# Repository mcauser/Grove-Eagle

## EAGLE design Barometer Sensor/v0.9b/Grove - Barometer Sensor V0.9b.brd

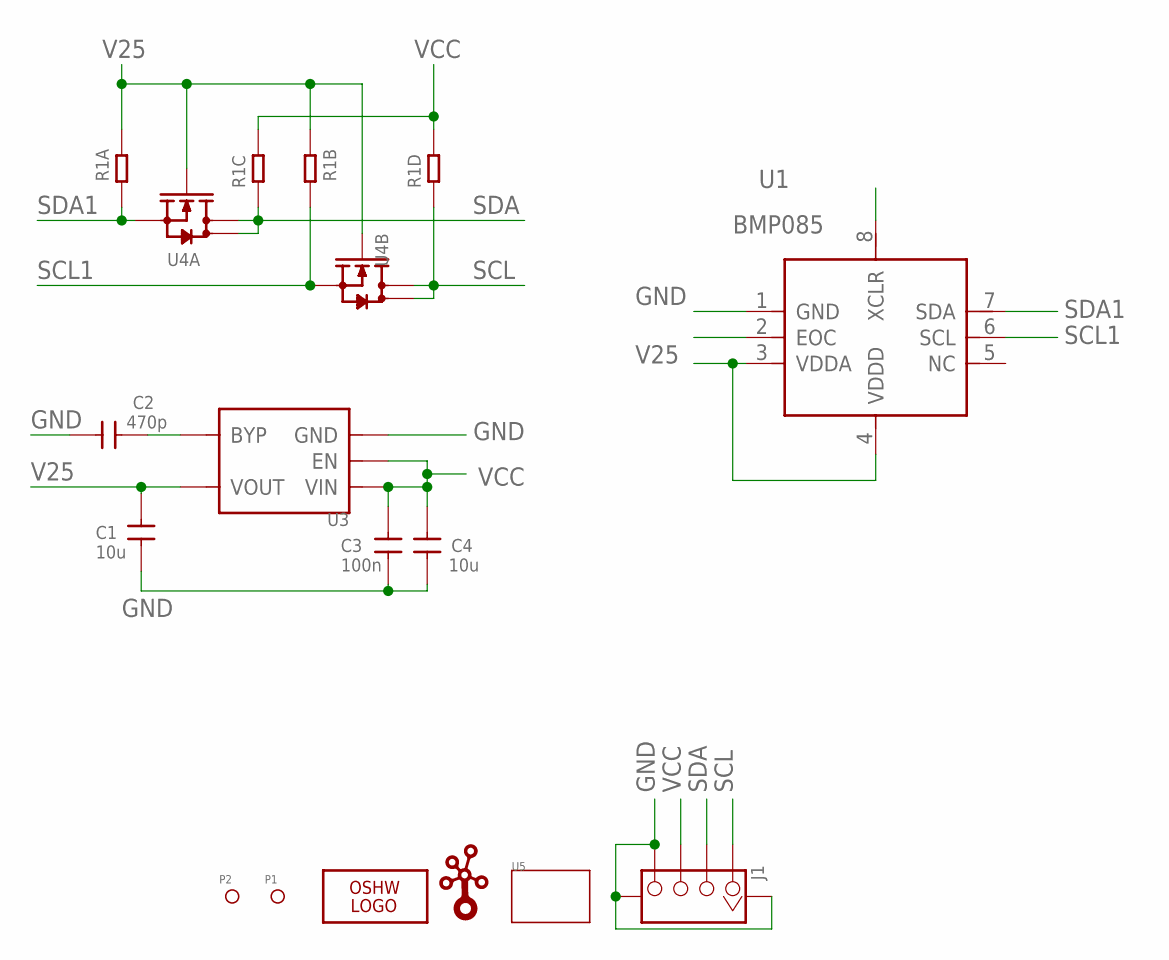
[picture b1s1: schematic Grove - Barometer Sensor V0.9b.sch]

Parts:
C1, C4: 10u; 0603
C2: 470p; 0603
C3: 100n; 0603
J1: TWIG-4P-2.0-SMD-FEMALE-REINFORCE'DD'; 4P-SMD-2.0
LOGO2: LOGO-OSHW-FILLX0200-NT; OSHW_FILLX200_NOTEXT
P1, P2: PAD-MARK; ROUND-MARK-0.635
R1: R-4R-1206; 1206-8-3.3X2.4
U1: BMP085; LCC8
U3: MIC5205; SOT23-5
U4: MOSFET-DUAL-N-1206-8; 1206-8
U5: TWIG-1U; 1U-DIM-W/-DRILL
U$1: LOGO-TWIGTWIGLOGO_SMALL; TWIGLOGO_SMALL

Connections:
GND: C1.2, C2.2, C3.1, C4.1, J1.4, J1.SS1, J1.SS2, U1.1 (GND), U3.2 (GND)
unnamed: C2.1, U3.4 (BYP)
SCL: J1.1, R1.4 (1), U4.5 (D), U4.6 (D)
SCL1: R1.7 (2), U1.6 (SCL), U4.3 (S)
SDA: J1.2, R1.3 (1), U4.7 (D), U4.8 (D)
SDA1: R1.1, U1.7 (SDA), U4.1 (S)
V25: C1.1, R1.2 (1), R1.8 (2), U1.3 (VDDA), U1.4 (VDDD), U3.5 (VOUT), U4.2 (G), U4.4 (G)
VCC: C3.2, C4.2, J1.3, R1.5 (2), R1.6 (2), U3.1 (VIN), U3.3 (EN)

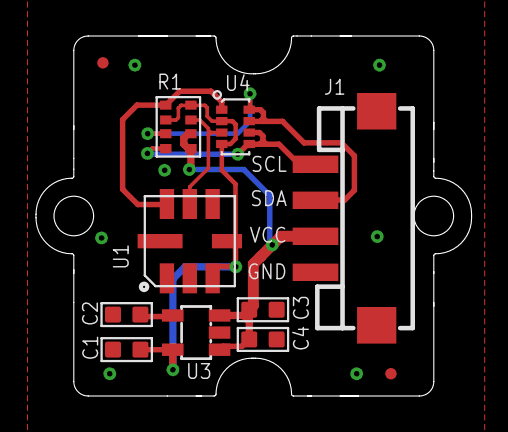
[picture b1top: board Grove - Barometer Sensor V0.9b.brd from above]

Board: 2 copper layers, 24.2 x 20.0 mm, 14 parts (2 on the bottom side), 8 nets.

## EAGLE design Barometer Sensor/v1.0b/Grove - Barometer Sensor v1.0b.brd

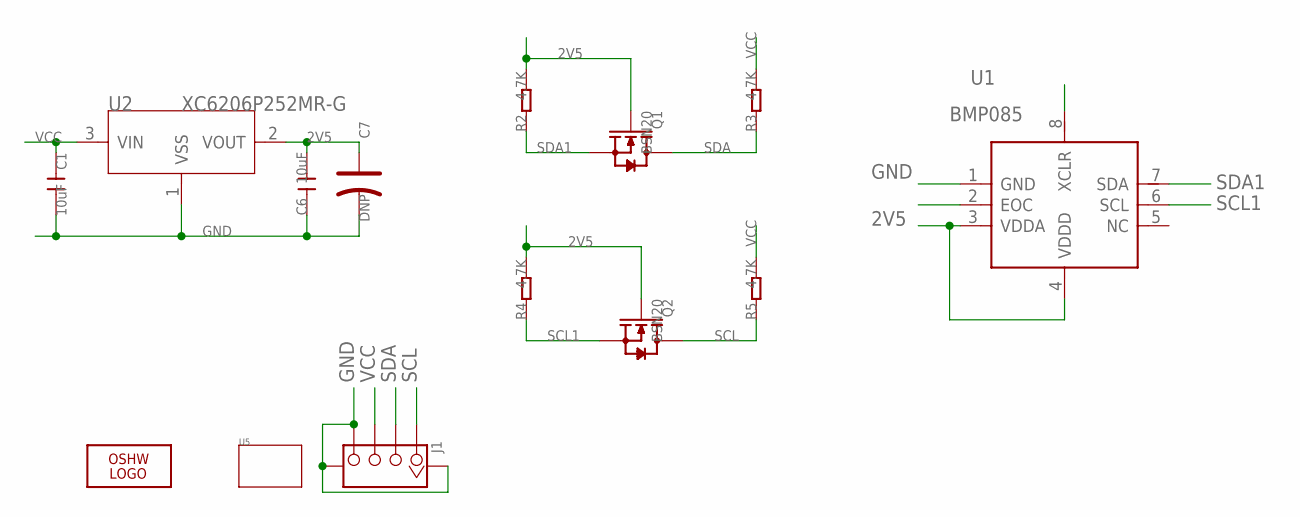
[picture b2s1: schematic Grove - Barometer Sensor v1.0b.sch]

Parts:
C1, C6: 10uF; C0805
C7: DNP; AVX-A
J1: TWIG-4P-2.0-SMD-FEMALE-REINFORCE'DD'; 4P-SMD-2.0
LOGO2: LOGO-OSHW-FILLX0200-NT; OSHW_FILLX200_NOTEXT
Q1, Q2: BSN20; SOT23
R2, R3, R4, R5: 4.7K; R0603
U1: BMP085; LCC8
U2: XC6206P252MR-G; SOT23
U5: TWIG-1U; 1U-DIM-W/-DRILL

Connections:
2V5: C6.2, C7.+, Q1.1 (G), Q2.1 (G), R2.2, R4.2, U1.3 (VDDA), U1.4 (VDDD), U2.2 (VOUT)
GND: C1.2, C6.1, C7.-, J1.4, J1.SS1, J1.SS2, U1.1 (GND), U2.1 (VSS)
SCL: J1.1, Q2.3 (D), R5.1
SCL1: Q2.2 (S), R4.1, U1.6 (SCL)
SDA: J1.2, Q1.3 (D), R3.1
SDA1: Q1.2 (S), R2.1, U1.7 (SDA)
VCC: C1.1, J1.3, R3.2, R5.2, U2.3 (VIN)

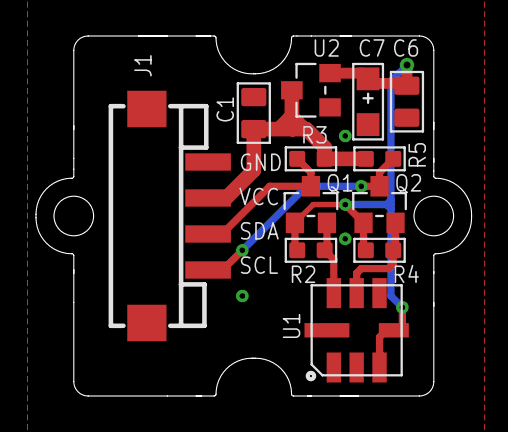
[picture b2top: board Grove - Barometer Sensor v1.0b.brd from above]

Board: 2 copper layers, 24.2 x 20.0 mm, 15 parts (2 on the bottom side), 7 nets.

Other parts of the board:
U$1: TWIGLOGO

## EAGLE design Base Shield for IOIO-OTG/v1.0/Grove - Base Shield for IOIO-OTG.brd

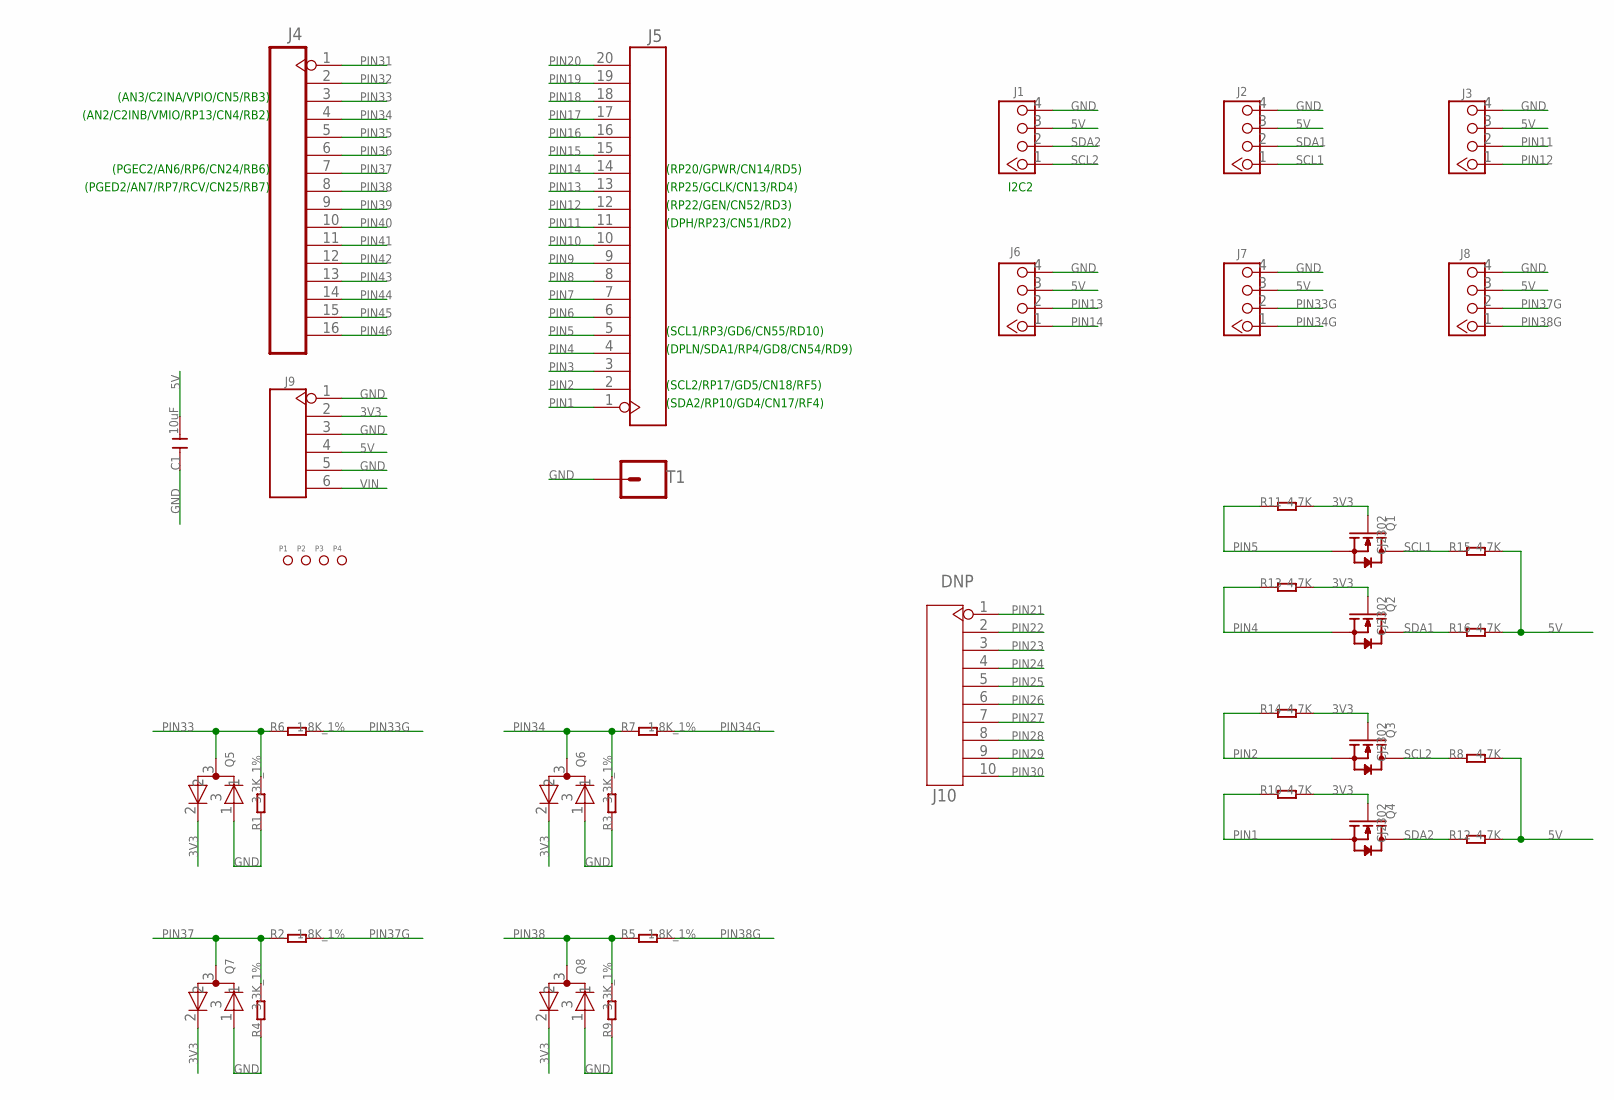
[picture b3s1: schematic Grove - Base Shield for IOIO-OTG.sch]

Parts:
C1: 10uF; C0805
J1, J2, J3, J6, J7, J8: TWIG-4P-2.0-2.0; 4P-2.0
J4: HEADER-16P-2.54; 16P-2.54
J5: HEADER-20P-2.54; 20P-2.54
J9: HEADER-6P-65/35MIL; 6P-2.54-65/35MIL
J10: DNP; 10P-2.54
P1, P2, P3, P4: PAD-MARK; ROUND-MARK-1.0
Q1, Q2, Q3, Q4: CJ2302; SOT23
Q5, Q6, Q7, Q8: BAV99; SOT23
R1, R3, R4, R9: 3.3K_1%; R0603
R2, R5, R6, R7: 1.8K_1%; R0603
R8, R10, R11, R12, R13, R14, R15, R16: 4.7K; R0603
T1: SPARKFUN_M01PTH; SPARKFUN_1X01

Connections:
3V3: J9.2, Q1.1 (G), Q2.1 (G), Q3.1 (G), Q4.1 (G), Q5.2, Q6.2, Q7.2, Q8.2, R10.2, R11.2, R13.2, R14.2
5V: C1.2, J1.3, J2.3, J3.3, J6.3, J7.3, J8.3, J9.4, R8.2, R12.2, R15.2, R16.2
GND: C1.1, J1.4, J2.4, J3.4, J6.4, J7.4, J8.4, J9.1, J9.3, J9.5, Q5.1, Q6.1, Q7.1, Q8.1, R1.1, R3.1, R4.1, R9.1, T1.1
PIN1: J5.1, Q4.2 (S), R10.1
PIN2: J5.2, Q3.2 (S), R14.1
PIN3: J5.3
PIN4: J5.4, Q2.2 (S), R13.1
PIN5: J5.5, Q1.2 (S), R11.1
PIN6: J5.6
PIN7: J5.7
PIN8: J5.8
PIN9: J5.9
PIN10: J5.10
PIN11: J3.2, J5.11
PIN12: J3.1, J5.12
PIN13: J5.13, J6.2
PIN14: J5.14, J6.1
PIN15: J5.15
PIN16: J5.16
PIN17: J5.17
PIN18: J5.18
PIN19: J5.19
PIN20: J5.20
PIN21: J10.1
PIN22: J10.2
PIN23: J10.3
PIN24: J10.4
PIN25: J10.5
PIN26: J10.6
PIN27: J10.7
PIN28: J10.8
PIN29: J10.9
PIN30: J10.10
PIN31: J4.1
PIN32: J4.2
PIN33: J4.3, Q5.3, R1.2, R6.1
PIN33G: J7.2, R6.2
PIN34: J4.4, Q6.3, R3.2, R7.1
PIN34G: J7.1, R7.2
PIN35: J4.5
PIN36: J4.6
PIN37: J4.7, Q7.3, R2.1, R4.2
PIN37G: J8.2, R2.2
PIN38: J4.8, Q8.3, R5.1, R9.2
PIN38G: J8.1, R5.2
PIN39: J4.9
PIN40: J4.10
PIN41: J4.11
PIN42: J4.12
PIN43: J4.13
PIN44: J4.14
PIN45: J4.15
PIN46: J4.16
SCL1: J2.1, Q1.3 (D), R15.1
SCL2: J1.1, Q3.3 (D), R8.1
SDA1: J2.2, Q2.3 (D), R16.1
SDA2: J1.2, Q4.3 (D), R12.1
VIN: J9.6

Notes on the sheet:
(SDA2/RP10/GD4/CN17/RF4)
(SCL2/RP17/GD5/CN18/RF5)
(SCL1/RP3/GD6/CN55/RD10)
(DPLN/SDA1/RP4/GD8/CN54/RD9)
(RP22/GEN/CN52/RD3)
(DPH/RP23/CN51/RD2)
(PGED2/AN7/RP7/RCV/CN25/RB7)
(PGEC2/AN6/RP6/CN24/RB6)
(RP20/GPWR/CN14/RD5)
(RP25/GCLK/CN13/RD4)
(AN2/C2INB/VMIO/RP13/CN4/RB2)
(AN3/C2INA/VPIO/CN5/RB3)
I2C2

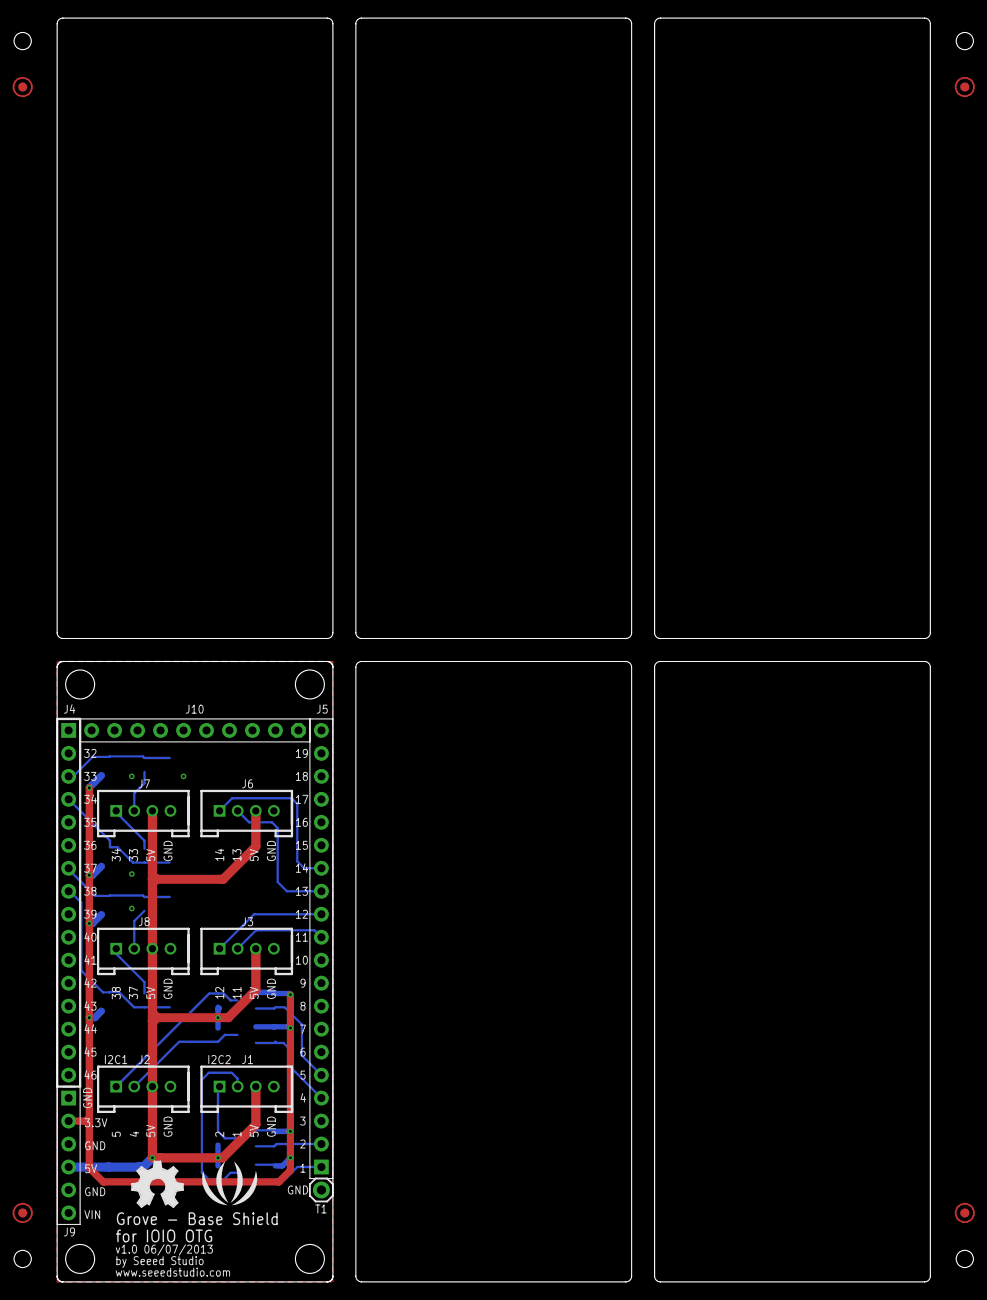
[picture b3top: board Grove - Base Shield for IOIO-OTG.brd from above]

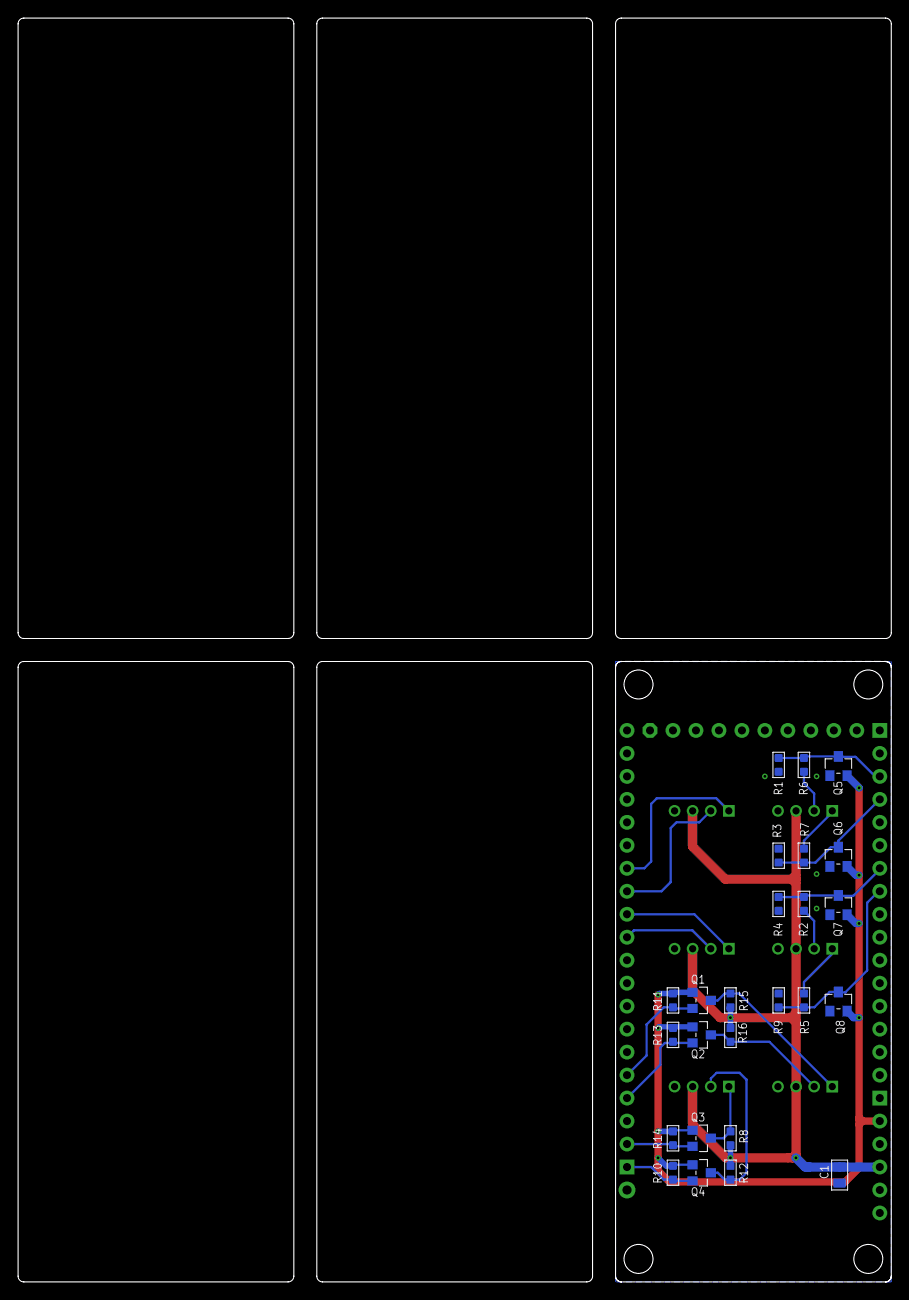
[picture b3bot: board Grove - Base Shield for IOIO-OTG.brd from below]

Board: 2 copper layers, 96.5 x 139.7 mm, 42 parts (25 on the bottom side), 23 nets.

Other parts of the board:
U$2: LOGO_SILK
U$3: OSHW_FILLX200_NOTEXT

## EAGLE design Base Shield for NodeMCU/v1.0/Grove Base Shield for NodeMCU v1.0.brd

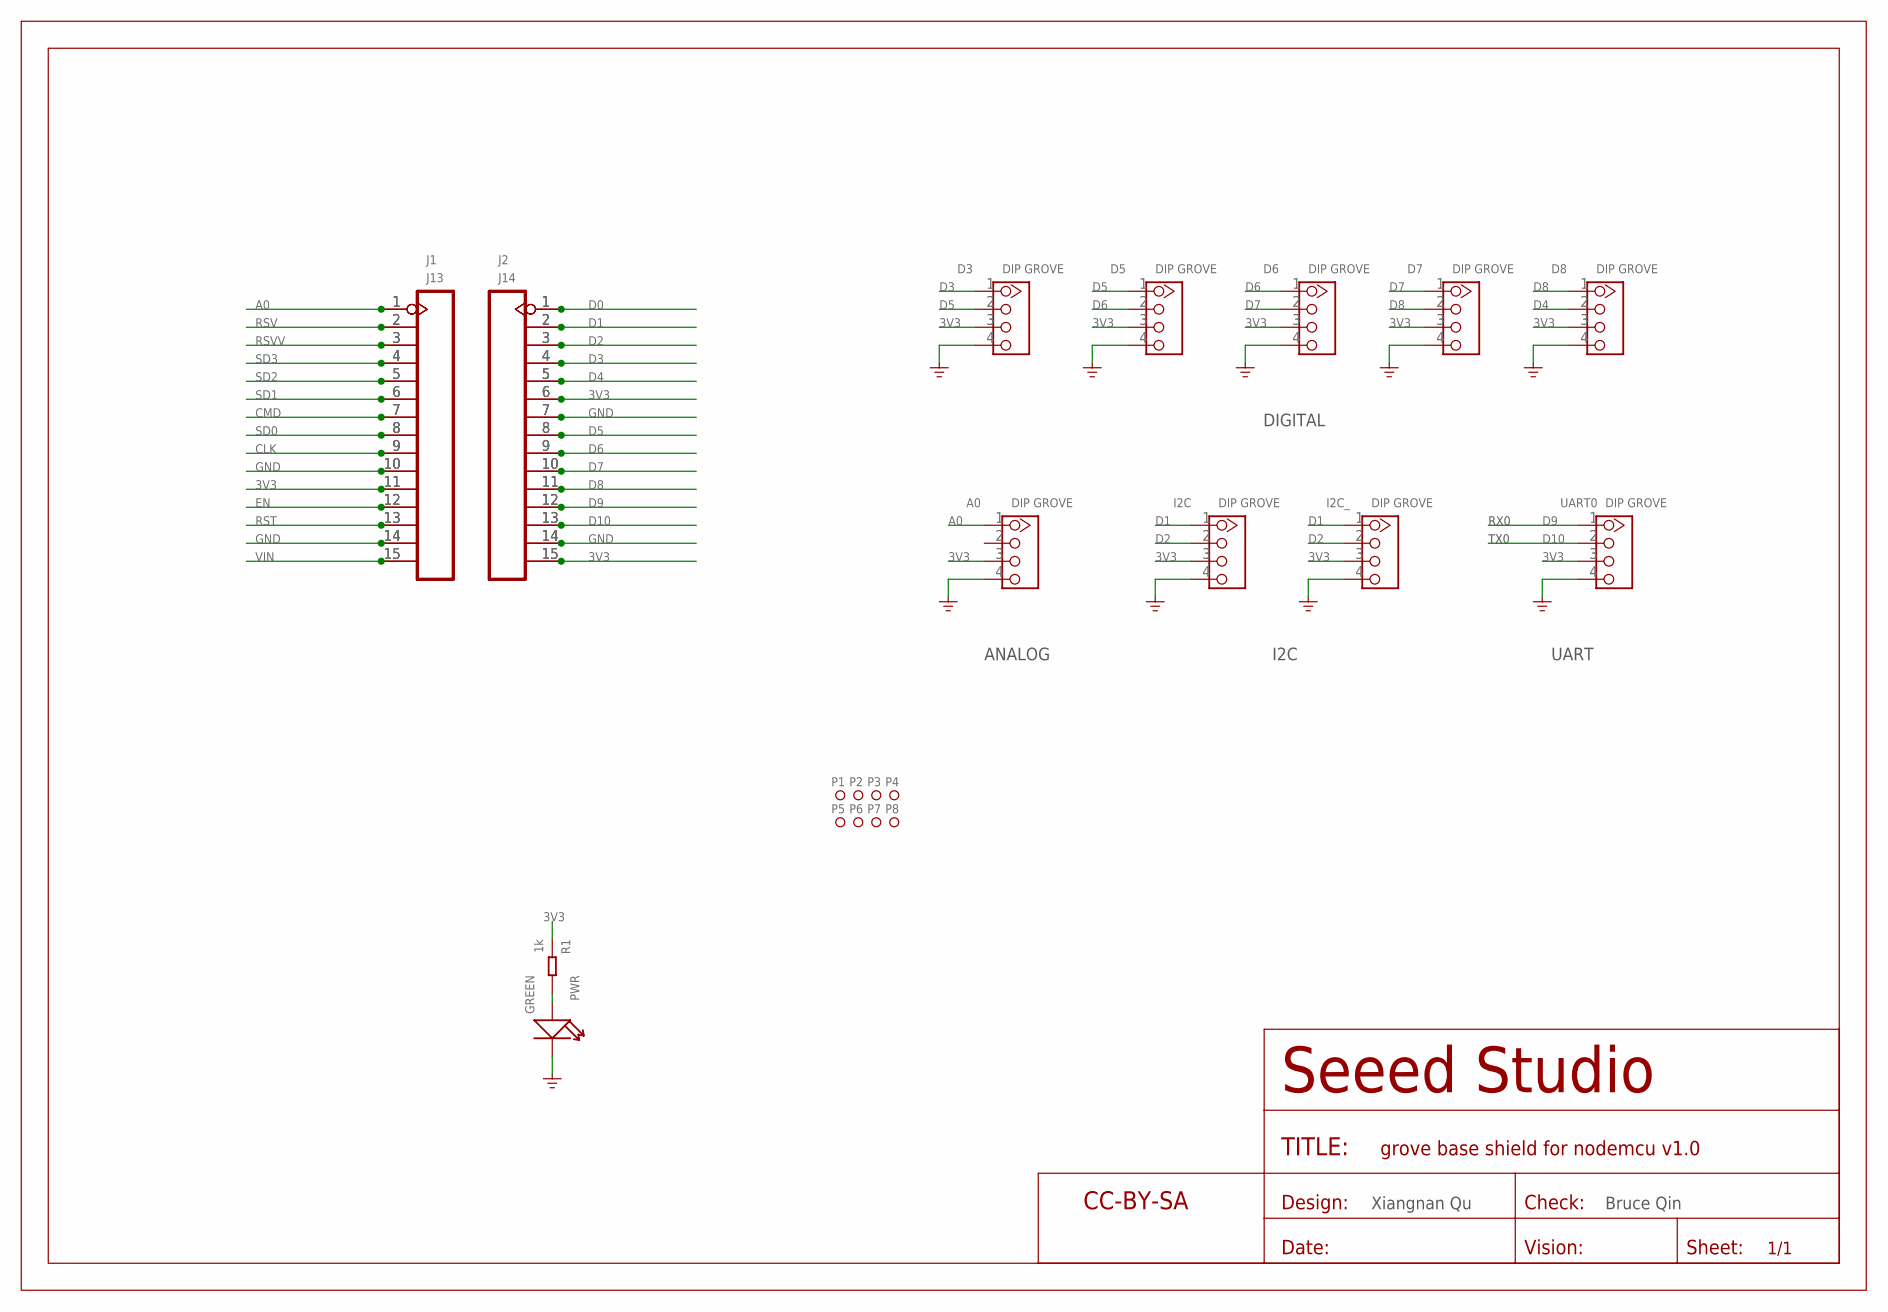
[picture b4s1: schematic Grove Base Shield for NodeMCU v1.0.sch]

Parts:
A0: DIP GROVE; HW4-2.0
D3, D5, D6, D7, D8: DIP GROVE; HW4-2.0
I2C, I2C_: DIP GROVE; HW4-2.0
J1, J2, J13, J14: HEADER-15P'2.54'; H15-2.54
P1, P2, P3, P4, P5, P6, P7, P8: MARK-1.0'ANNULAR'; ROUND-MARK-1.0
PWR: GREEN; LED-0603
R1: 1k; R0603
U$7: SEEEDSTUDIO-OPEN-SCH-FRAME; SEEEDSTUDIO-PCB-FRAME
UART0: DIP GROVE; HW4-2.0

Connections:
3V3: A0.3, D3.3, D5.3, D6.3, D7.3, D8.3, I2C.3, I2C_.3, J1.11, J2.6, J2.15, J13.11, J14.6, J14.15, R1.1, UART0.3
A0: A0.1, J1.1, J13.1
CLK: J1.9, J13.9
CMD: J1.7, J13.7
D0: J2.1, J14.1
D1: I2C.1, I2C_.1, J2.2, J14.2
D2: I2C.2, I2C_.2, J2.3, J14.3
D3: D3.1, J2.4, J14.4
D4: D8.2, J2.5, J14.5
D5: D3.2, D5.1, J2.8, J14.8
D6: D5.2, D6.1, J2.9, J14.9
D7: D6.2, D7.1, J2.10, J14.10
D8: D7.2, D8.1, J2.11, J14.11
D9: J2.12, J14.12, UART0.1
D10: J2.13, J14.13, UART0.2
EN: J1.12, J13.12
GND: A0.4, D3.4, D5.4, D6.4, D7.4, D8.4, I2C.4, I2C_.4, J1.10, J1.14, J2.7, J2.14, J13.10, J13.14, J14.7, J14.14, PWR.-, UART0.4
unnamed: PWR.+, R1.2
RST: J1.13, J13.13
RSV: J1.2, J13.2
RSVV: J1.3, J13.3
SD0: J1.8, J13.8
SD1: J1.6, J13.6
SD2: J1.5, J13.5
SD3: J1.4, J13.4
VIN: J1.15, J13.15

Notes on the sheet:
Xiangnan Qu
Bruce Qin
UART
TX0
RX0
I2C
ANALOG
DIGITAL

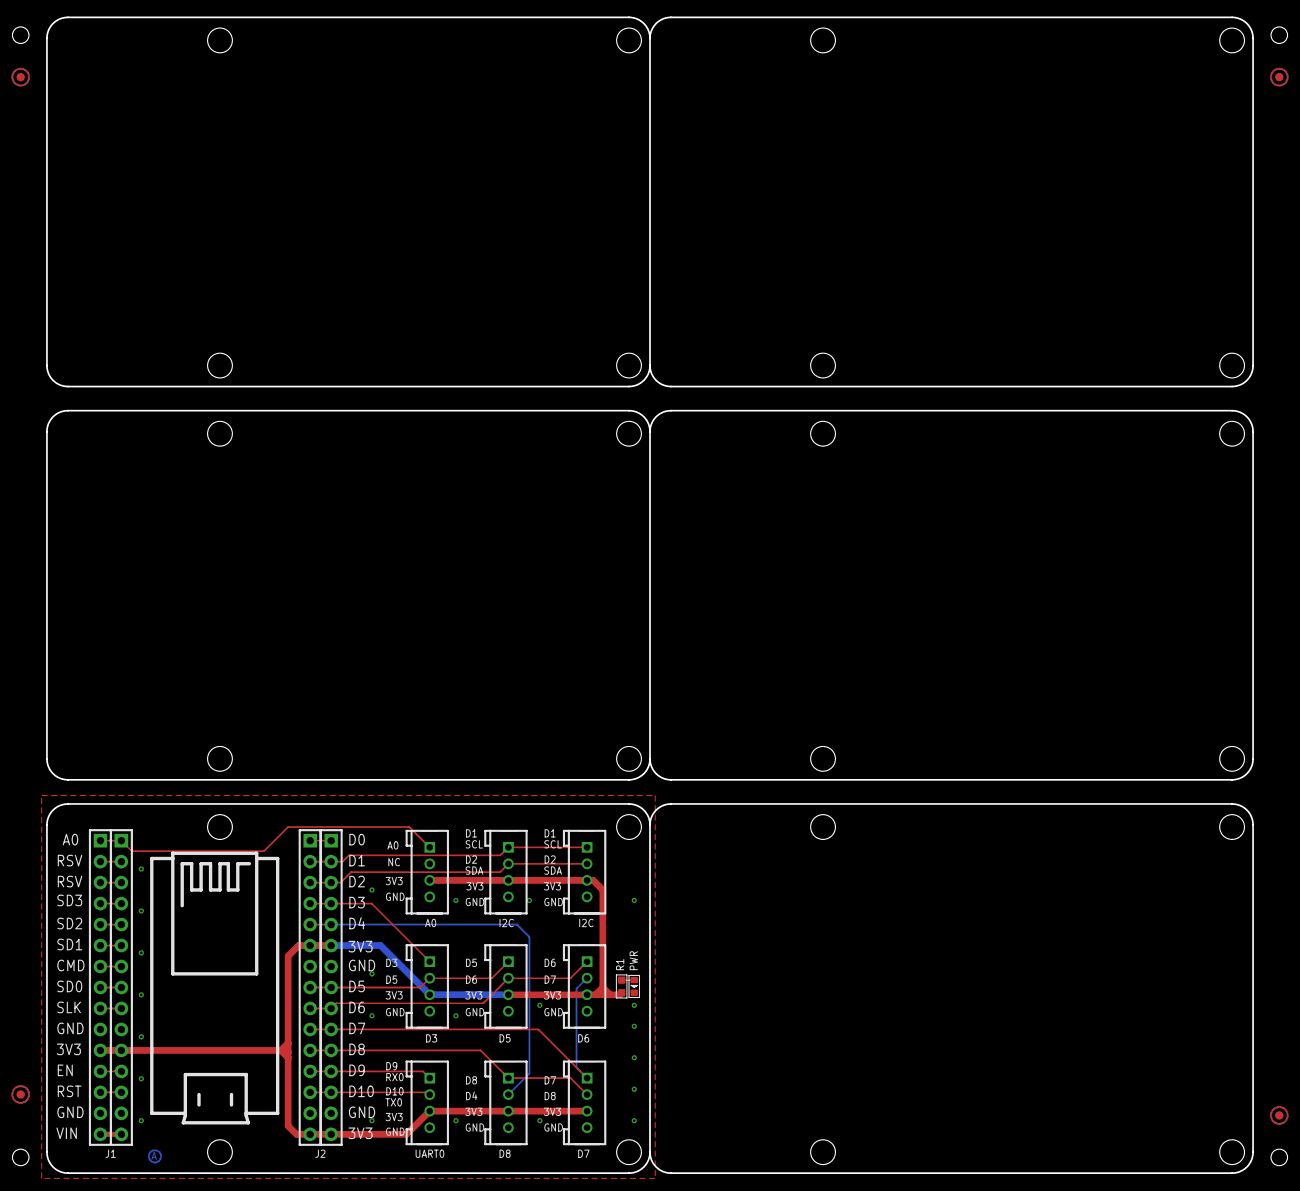
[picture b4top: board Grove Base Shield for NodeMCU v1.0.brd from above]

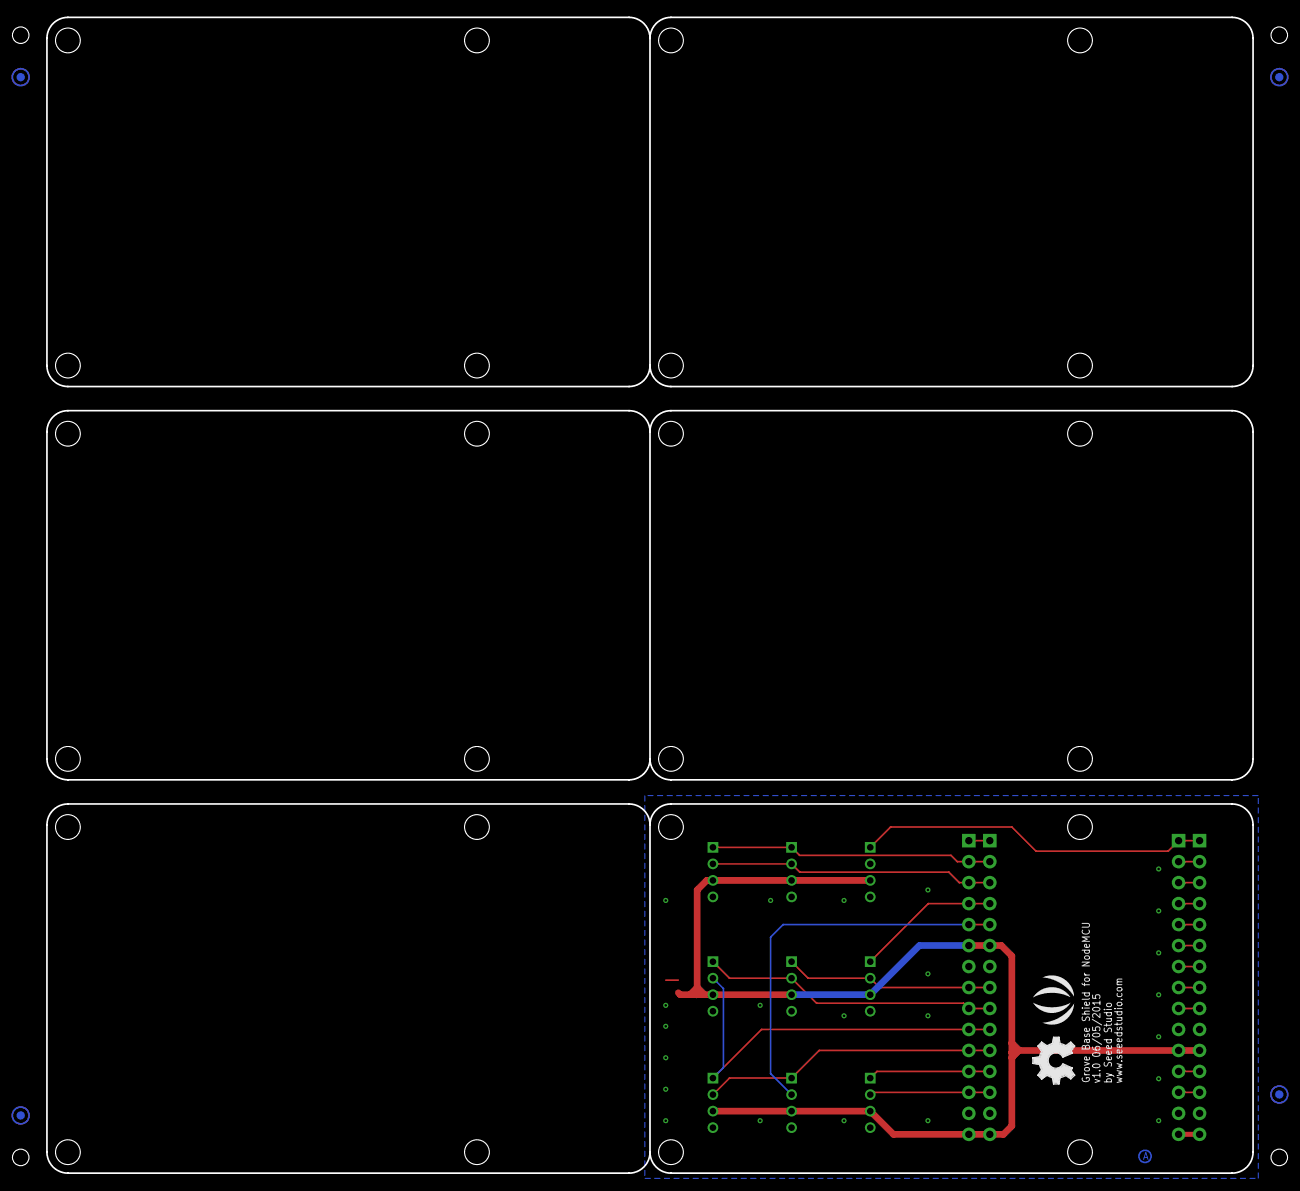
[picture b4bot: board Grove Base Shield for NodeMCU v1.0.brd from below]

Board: 2 copper layers, 146.1 x 140.0 mm, 26 parts (6 on the bottom side), 26 nets.

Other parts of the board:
U$27: OSHW_FILLX200_NOTEXT
U$29: SEEED-SILK-280*268MIL

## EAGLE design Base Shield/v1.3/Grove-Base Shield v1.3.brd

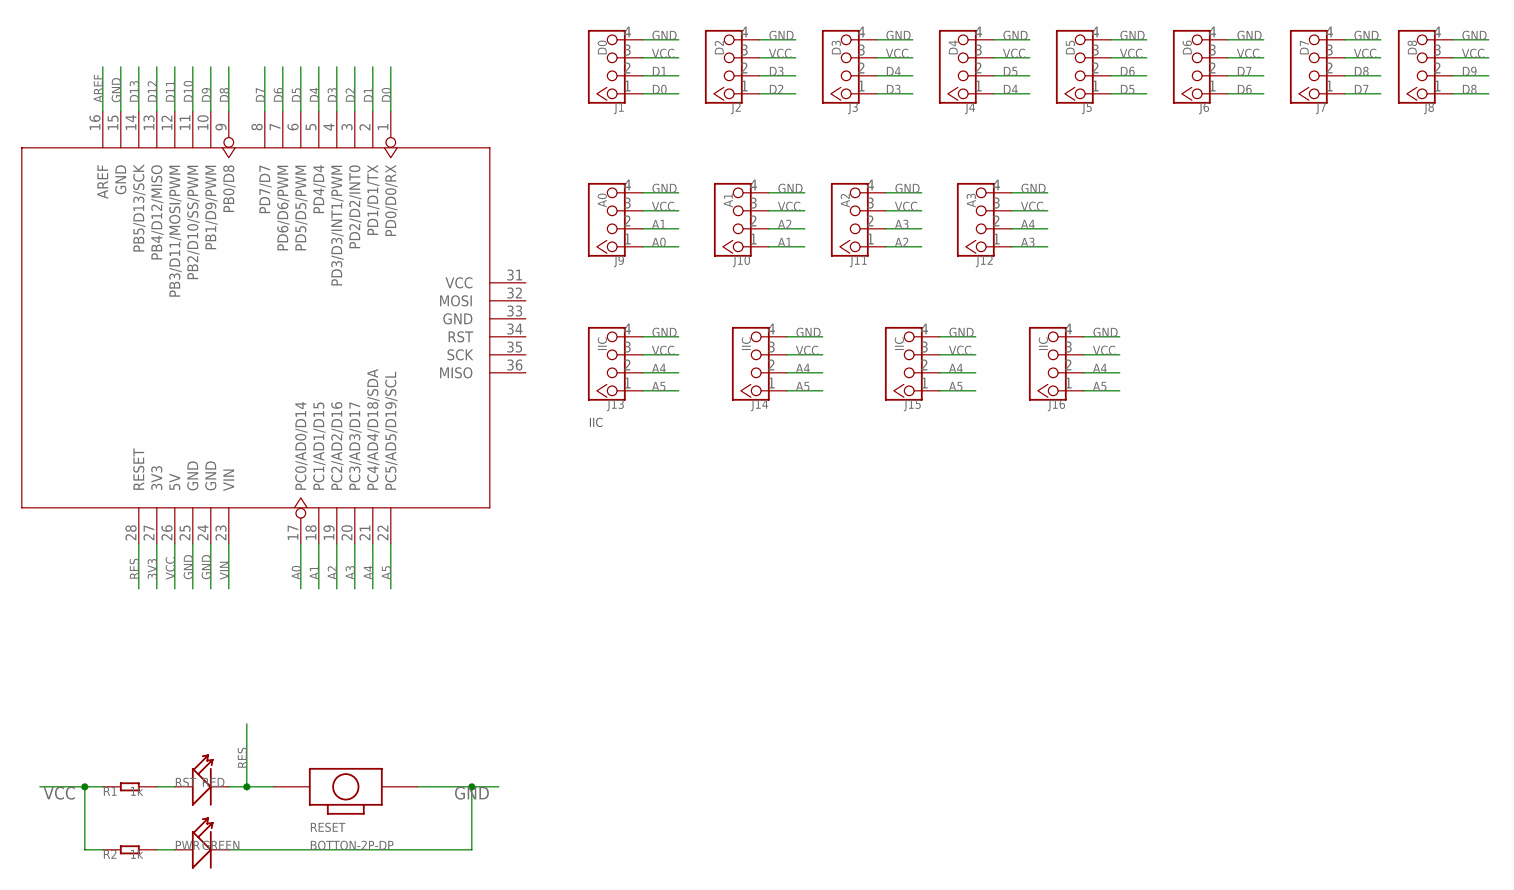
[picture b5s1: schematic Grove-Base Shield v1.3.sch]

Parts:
J1: D0; 4P-2.0
J2: D2; 4P-2.0
J3: D3; 4P-2.0
J4: D4; 4P-2.0
J5: D5; 4P-2.0
J6: D6; 4P-2.0
J7: D7; 4P-2.0
J8: D8; 4P-2.0
J9: A0; 4P-2.0-90D
J10: A1; 4P-2.0-90D
J11: A2; 4P-2.0-90D
J12: A3; 4P-2.0-90D
J13, J14, J15, J16: IIC; 4P-2.0
PWR: GREEN; LED-2P-2.54-3MM
R1, R2: 1k; R0204/7
RESET: BOTTON-2P-DP; 2P-7.62X3.56-90D
RST: RED; LED-2P-2.54-3MM
U1: ARDUINO'W/O-SILK'; ARDUINO-W/O-SILK

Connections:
3V3: U1.27 (3V3)
A0: J9.1, U1.17 (PC0/AD0/D14)
A1: J9.2, J10.1, U1.18 (PC1/AD1/D15)
A2: J10.2, J11.1, U1.19 (PC2/AD2/D16)
A3: J11.2, J12.1, U1.20 (PC3/AD3/D17)
A4: J12.2, J13.2, J14.2, J15.2, J16.2, U1.21 (PC4/AD4/D18/SDA)
A5: J13.1, J14.1, J15.1, J16.1, U1.22 (PC5/AD5/D19/SCL)
AREF: U1.16 (AREF)
D0: J1.1, U1.1 (PD0/D0/RX)
D1: J1.2, U1.2 (PD1/D1/TX)
D2: J2.1, U1.3 (PD2/D2/INT0)
D3: J2.2, J3.1, U1.4 (PD3/D3/INT1/PWM)
D4: J3.2, J4.1, U1.5 (PD4/D4)
D5: J4.2, J5.1, U1.6 (PD5/D5/PWM)
D6: J5.2, J6.1, U1.7 (PD6/D6/PWM)
D7: J6.2, J7.1, U1.8 (PD7/D7)
D8: J7.2, J8.1, U1.9 (PB0/D8)
D9: J8.2, U1.10 (PB1/D9/PWM)
D10: U1.11 (PB2/D10/SS/PWM)
D11: U1.12 (PB3/D11/MOSI/PWM)
D12: U1.13 (PB4/D12/MISO)
D13: U1.14 (PB5/D13/SCK)
GND: J1.4, J2.4, J3.4, J4.4, J5.4, J6.4, J7.4, J8.4, J9.4, J10.4, J11.4, J12.4, J13.4, J14.4, J15.4, J16.4, PWR.K (-), RESET.P$2 (2), U1.15 (GND), U1.24 (GND), U1.25 (GND)
unnamed: PWR.A (+), R2.2
unnamed: R1.2, RST.A (+)
RES: RESET.P$1 (1), RST.K (-), U1.28 (RESET)
VCC: J1.3, J2.3, J3.3, J4.3, J5.3, J6.3, J7.3, J8.3, J9.3, J10.3, J11.3, J12.3, J13.3, J14.3, J15.3, J16.3, R1.1, R2.1, U1.26 (5V)
VIN: U1.23 (VIN)

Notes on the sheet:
IIC

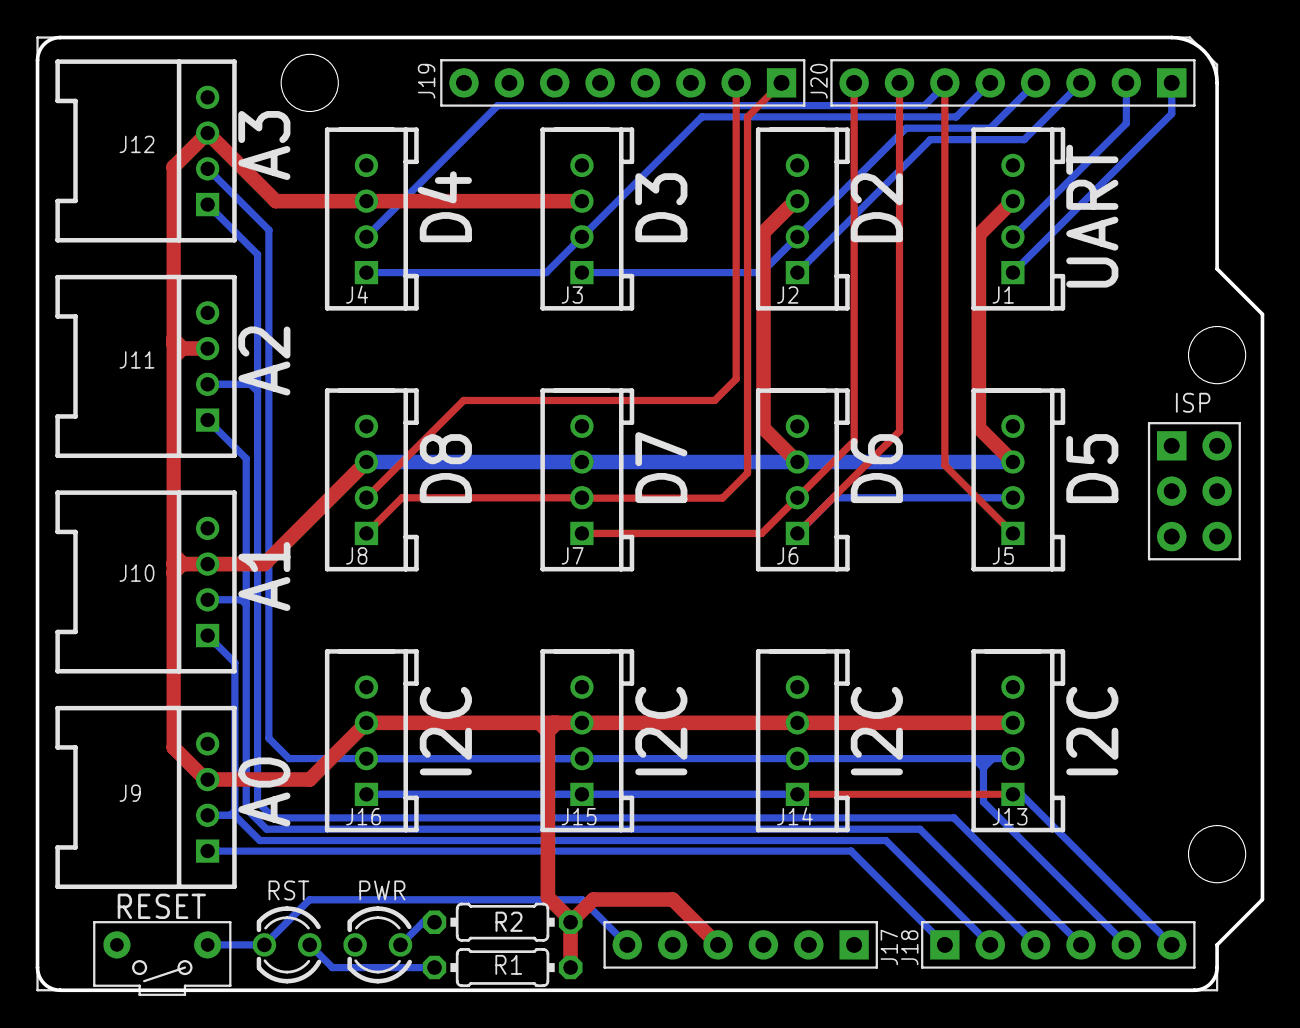
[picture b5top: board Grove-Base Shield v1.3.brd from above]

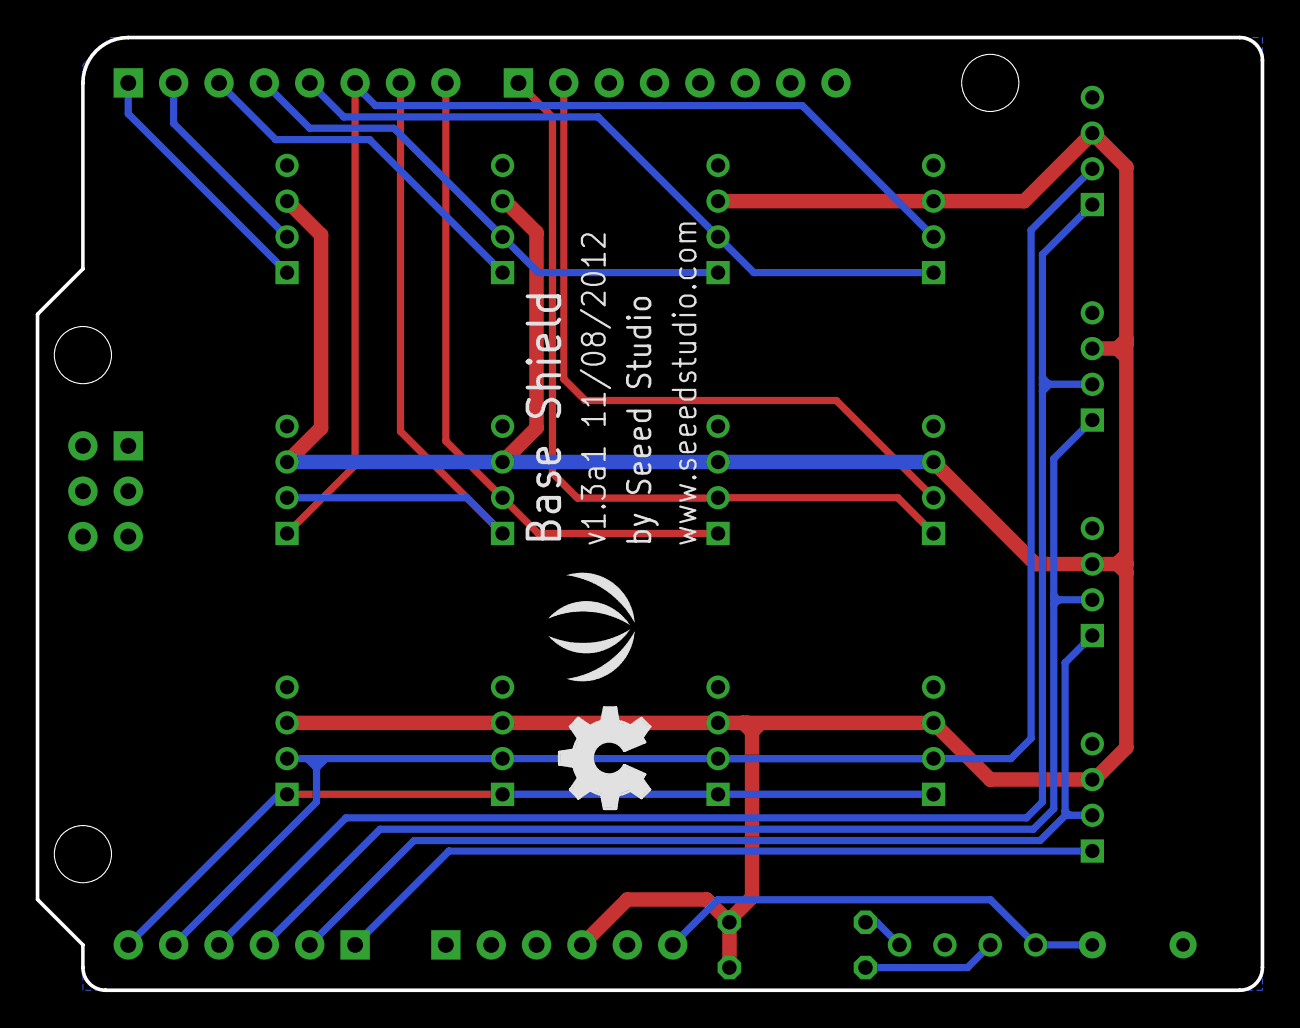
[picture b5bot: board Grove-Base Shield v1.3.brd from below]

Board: 2 copper layers, 68.6 x 53.3 mm, 24 parts (2 on the bottom side), 21 nets.

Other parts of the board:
U$2: OSHW_FILLX200_NOTEXT
U$4: LOGO_SILK

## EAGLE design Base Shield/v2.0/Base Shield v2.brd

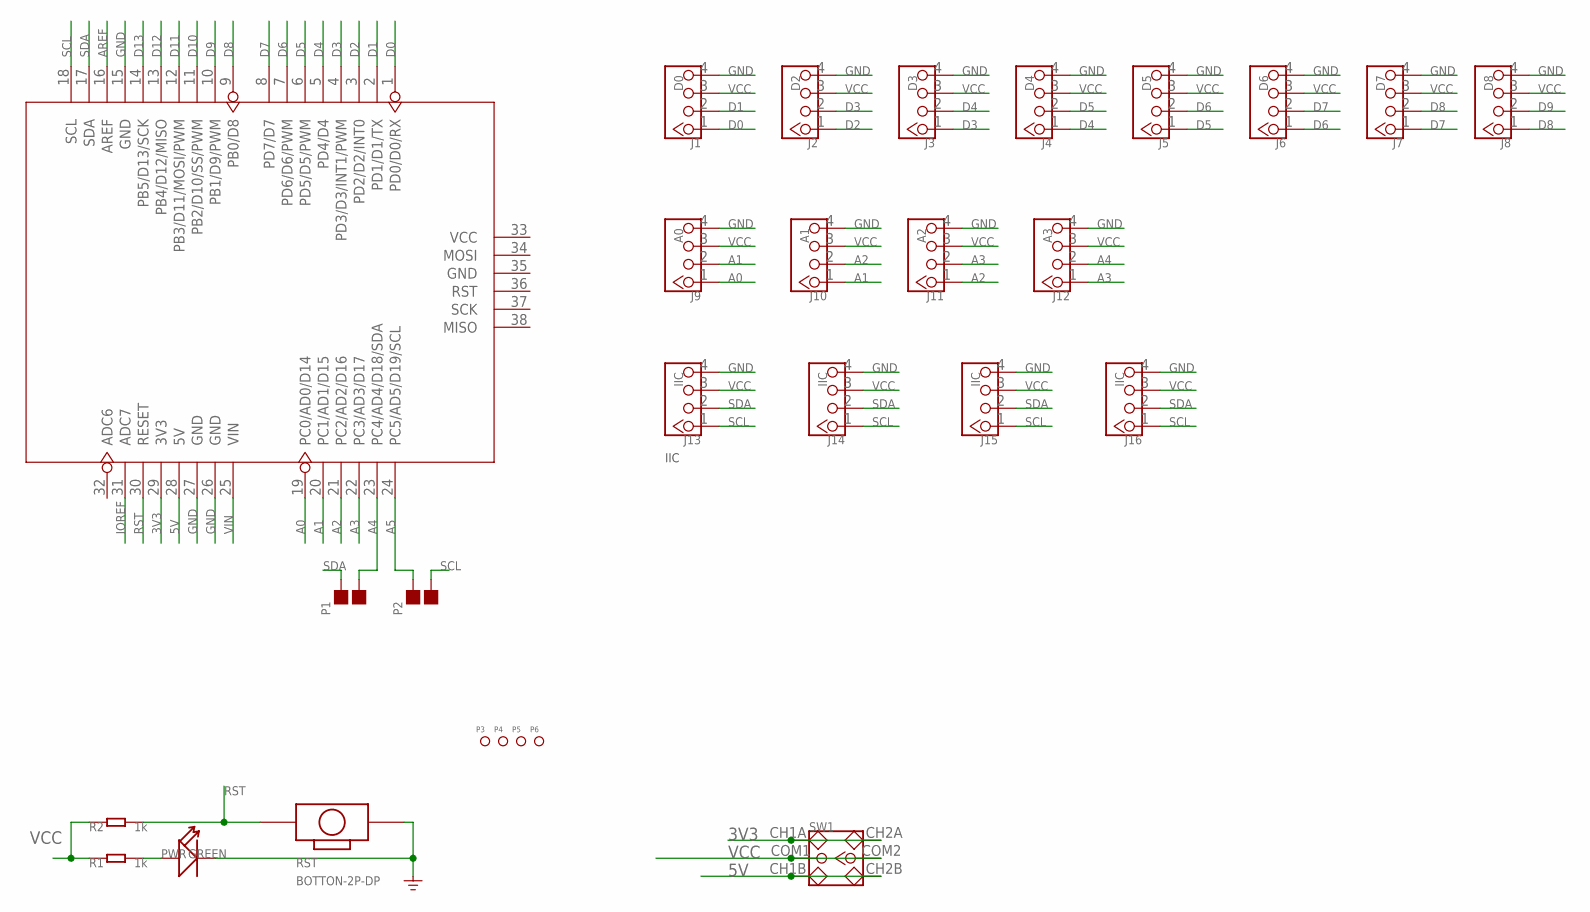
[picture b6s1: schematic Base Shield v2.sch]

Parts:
J1: D0; 4P-2.0
J2: D2; 4P-2.0
J3: D3; 4P-2.0
J4: D4; 4P-2.0
J5: D5; 4P-2.0
J6: D6; 4P-2.0
J7: D7; 4P-2.0
J8: D8; 4P-2.0
J9: A0; 4P-2.0-90D
J10: A1; 4P-2.0-90D
J11: A2; 4P-2.0-90D
J12: A3; 4P-2.0-90D
J13, J14, J15, J16: IIC; 4P-2.0
P1, P2: DNP; 2P-SMD-1.78X1.27
P3, P4, P5, P6: PAD-MARK; ROUND-MARK-1.0
PWR: GREEN; LED-2P-2.54-3MM
R1, R2: 1k; R0603
RST: BOTTON-2P-DP; 2P-7.62X3.56-90D
SW1: SWITCH-2CH-6P'90D'; 6P-2CH-2.5-9.1X3.5X3.2H-90D
U2: DIP Long Blue Female Header; ARDUINO-38P

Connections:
3V3: SW1.CH1A, SW1.CH2A, U2.29 (3V3)
5V: SW1.CH1B, SW1.CH2B, U2.28 (5V)
A0: J9.1, U2.19 (PC0/AD0/D14)
A1: J9.2, J10.1, U2.20 (PC1/AD1/D15)
A2: J10.2, J11.1, U2.21 (PC2/AD2/D16)
A3: J11.2, J12.1, U2.22 (PC3/AD3/D17)
A4: J12.2, P1.1, U2.23 (PC4/AD4/D18/SDA)
A5: P2.2, U2.24 (PC5/AD5/D19/SCL)
AREF: U2.16 (AREF)
D0: J1.1, U2.1 (PD0/D0/RX)
D1: J1.2, U2.2 (PD1/D1/TX)
D2: J2.1, U2.3 (PD2/D2/INT0)
D3: J2.2, J3.1, U2.4 (PD3/D3/INT1/PWM)
D4: J3.2, J4.1, U2.5 (PD4/D4)
D5: J4.2, J5.1, U2.6 (PD5/D5/PWM)
D6: J5.2, J6.1, U2.7 (PD6/D6/PWM)
D7: J6.2, J7.1, U2.8 (PD7/D7)
D8: J7.2, J8.1, U2.9 (PB0/D8)
D9: J8.2, U2.10 (PB1/D9/PWM)
D10: U2.11 (PB2/D10/SS/PWM)
D11: U2.12 (PB3/D11/MOSI/PWM)
D12: U2.13 (PB4/D12/MISO)
D13: U2.14 (PB5/D13/SCK)
GND: J1.4, J2.4, J3.4, J4.4, J5.4, J6.4, J7.4, J8.4, J9.4, J10.4, J11.4, J12.4, J13.4, J14.4, J15.4, J16.4, PWR.K (-), RST.P$2 (2), U2.15 (GND), U2.26 (GND), U2.27 (GND)
IOREF: U2.31 (ADC7)
unnamed: PWR.A (+), R1.2
RST: R2.2, RST.P$1 (1), U2.30 (RESET)
SCL: J13.1, J14.1, J15.1, J16.1, P2.1, U2.18 (SCL)
SDA: J13.2, J14.2, J15.2, J16.2, P1.2, U2.17 (SDA)
VCC: J1.3, J2.3, J3.3, J4.3, J5.3, J6.3, J7.3, J8.3, J9.3, J10.3, J11.3, J12.3, J13.3, J14.3, J15.3, J16.3, R1.1, R2.1, SW1.COM1, SW1.COM2
VIN: U2.25 (VIN)

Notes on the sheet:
IIC

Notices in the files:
parts and their libraries:
moudle-new: This work is licensed under the Creative Commons Attribution 4.0 International License.
To view a copy of this license,visit:
http://creativecommons.org/licenses/by-sa/4.0
moudle-new: CC-BY-SA
